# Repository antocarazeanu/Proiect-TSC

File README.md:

## README - Proiect TSC 2025
## Titlu Proiect: Ebook Reader
## Nume: Carazeanu Antonio-Christian
## Grupa: 332CC

Cuprins:

0. Descrierea generala
1. Diagrama bloc
2. BOM - Bill of Materials
3. Arhitectura hardware
4. Pini utilizați pe ESP32-C6 și justificare
5. Probleme intampinate
6. Observatii

## 0. Descriere Generală:
Proiectul a avut ca scop realizarea unui Ebook Reader ieftin si OpenSource din
perspectiva unui Arhitect de Sistem. Acest dispozitiv poate fi scos pentru a fi
produs in masa.

Am urmat toți pașii standard de proiectare, începând de la schematic, continuând
cu layout-ul PCB, modelare 3D și integrarea finală într-o carcasă.

## 1. Diagrama bloc

## 2. BOM - Bill of Materials
| Device | Value | Check_Price | Datasheet |
|--------|-------|-------------|-----------|
| ADAFRUIT_LEDCHIP-LED0603 | - | [Link](https://www.snapeda.com/parts/KP-1608SURCK/Kingbright/view-part/?ref=search&t=LED%200603) | [Link](https://www.snapeda.com/parts/KP-1608SURCK/Kingbright/datasheet/) |
| SJ | - | [Link](https://grabcad.com/library/solder-jumpers-1) | - |
| EAGLE-LTSPICE_C | 0.1uF/50V | [Link](https://componentsearchengine.com/part-view/CC0402MRX5R5BB106/YAGEO) | [Link](https://componentsearchengine.com/Datasheets/2/CC0402MRX5R5BB106.pdf) |
| ESP32_WROVER_EAGLE-LTSPICE_R | 0.47 | [Link](https://componentsearchengine.com/part-view/R0402%201%25%20100%20K%20(RC0402FR-07100KL)/YAGEO) | [Link](https://www.yageo.com/upload/media/product/products/datasheet/rchip/PYu-RC_Group_51_RoHS_L_12.pdf) |
| ESP32_WROVER_EAGLE-LTSPICE_R | 100K | [Link](https://componentsearchengine.com/part-view/R0402%201%25%20100%20K%20(RC0402FR-07100KL)/YAGEO) | [Link](https://www.yageo.com/upload/media/product/products/datasheet/rchip/PYu-RC_Group_51_RoHS_L_12.pdf) |
| EAGLE-LTSPICE_C | 100nF | [Link](https://componentsearchengine.com/part-view/CC0402MRX5R5BB106/YAGEO) | [Link](https://componentsearchengine.com/Datasheets/2/CC0402MRX5R5BB106.pdf) |
| RCL_CPOL-EUCT3528 | 100uF TANT | [Link](https://www.snapeda.com/parts/TAJB475K025RNJ/AVX/view-part/?ref=dk&t=capacitor%203528&con_ref=None) | [Link](https://s3.amazonaws.com/snapeda/datasheet/TAJB475K025RNJ_AVX.pdf) |
| ESP32_WROVER_EAGLE-LTSPICE_R | 10K | [Link](https://componentsearchengine.com/part-view/R0402%201%25%20100%20K%20(RC0402FR-07100KL)/YAGEO) | [Link](https://www.yageo.com/upload/media/product/products/datasheet/rchip/PYu-RC_Group_51_RoHS_L_12.pdf) |
| EAGLE-LTSPICE_C | 10uF | [Link](https://componentsearchengine.com/part-view/CC0402MRX5R5BB106/YAGEO) | [Link](https://componentsearchengine.com/Datasheets/2/CC0402MRX5R5BB106.pdf) |
| 112A-TAAR-R03_ATTEND | 112A-TAAR-R03_ATTEND | [Link](https://store.comet.srl.ro/Catalogue/Product/43497/) | [Link](https://store.comet.bg/download-file.php?id=8824) |
| ESP32_WROVER_EAGLE-LTSPICE_R | 15 | [Link](https://componentsearchengine.com/part-view/R0402%201%25%20100%20K%20(RC0402FR-07100KL)/YAGEO) | [Link](https://www.yageo.com/upload/media/product/products/datasheet/rchip/PYu-RC_Group_51_RoHS_L_12.pdf) |
| EAGLE-LTSPICE_C | 1uF | [Link](https://componentsearchengine.com/part-view/CC0402MRX5R5BB106/YAGEO) | [Link](https://componentsearchengine.com/Datasheets/2/CC0402MRX5R5BB106.pdf) |
| EAGLE-LTSPICE_C | 1uF/50V | [Link](https://componentsearchengine.com/part-view/CC0402MRX5R5BB106/YAGEO) | [Link](https://componentsearchengine.com/Datasheets/2/CC0402MRX5R5BB106.pdf) |
| ESP32_WROVER_EAGLE-LTSPICE_R | 2.2 | [Link](https://componentsearchengine.com/part-view/R0402%201%25%20100%20K%20(RC0402FR-07100KL)/YAGEO) | [Link](https://www.yageo.com/upload/media/product/products/datasheet/rchip/PYu-RC_Group_51_RoHS_L_12.pdf) |
| ESP32_WROVER_EAGLE-LTSPICE_R | 200 | [Link](https://componentsearchengine.com/part-view/R0402%201%25%20100%20K%20(RC0402FR-07100KL)/YAGEO) | [Link](https://www.yageo.com/upload/media/product/products/datasheet/rchip/PYu-RC_Group_51_RoHS_L_12.pdf) |
| ESP32_WROVER_SPARKFUN-DISCRETESEMI_MOSFET_PCH-DMG2305UX-7 | 20V/4.2A/52m?/1.4W | [Link](https://componentsearchengine.com/part-view/DMG2305UX-7/Diodes%20Incorporated) | [Link](https://www.diodes.com//assets/Datasheets/DMG2305UX.pdf) |
| ESP32_WROVER_EAGLE-LTSPICE_R | 2K | [Link](https://componentsearchengine.com/part-view/R0402%201%25%20100%20K%20(RC0402FR-07100KL)/YAGEO) | [Link](https://www.yageo.com/upload/media/product/products/datasheet/rchip/PYu-RC_Group_51_RoHS_L_12.pdf) |
| EAGLE-LTSPICE_C | 4.7uF | [Link](https://componentsearchengine.com/part-view/CC0402MRX5R5BB106/YAGEO) | [Link](https://componentsearchengine.com/Datasheets/2/CC0402MRX5R5BB106.pdf) |
| EAGLE-LTSPICE_C | 4.7uF/25V | [Link](https://componentsearchengine.com/part-view/CC0402MRX5R5BB106/YAGEO) | [Link](https://componentsearchengine.com/Datasheets/2/CC0402MRX5R5BB106.pdf) |
| ESP32_WROVER_EAGLE-LTSPICE_R | 5k1 | [Link](https://componentsearchengine.com/part-view/R0402%201%25%20100%20K%20(RC0402FR-07100KL)/YAGEO) | [Link](https://www.yageo.com/upload/media/product/products/datasheet/rchip/PYu-RC_Group_51_RoHS_L_12.pdf) |
| 744043680IND_4828-WE-TPC_WRE | 68uH | [Link](https://ro.mouser.com/ProductDetail/Wurth-Elektronik/744043680?qs=PGXP4M47uW6VkZq%252BkzjrHA%3D%3D&_gl=1*5xajdn*_ga*MzY2ODgyMjE4LjE3NDM2NzQxODk.*_ga_15W4STQT4T*MTc0Mzg3MzkxMy40LjAuMTc0Mzg3MzkxNi41Ny4wLjA.) | [Link](https://www.we-online.com/components/products/datasheet/744043680.pdf) |
| BD5229G-TR | BD5229G-TR | [Link](https://componentsearchengine.com/part-view/BD5229G-TR/ROHM%20Semiconductor) | [Link](https://datasheet.datasheetarchive.com/originals/distributors/Datasheets_SAMA/f2b9741ef86007909f138d561a359946.pdf) |
| ESP32_WROVER_BME680_BME680 | BME688 | [Link](https://www.snapeda.com/parts/BME680/Bosch/view-part/?welcome=home) | [Link](https://www.snapeda.com/parts/BME680/Bosch%20Sensortec/datasheet/) |
| BUTTON_CUSYOMV1V2 | BUTTON_CUSYOMV1V2 | [Link](https://industry.panasonic.com/global/en/products/control/switch/light-touch/number/evqpuj02k) | [Link](https://industry.panasonic.com/global/en/downloads?tab=catalog&small_g_cd=203&part_no=EVQPUJ02K) |
| CPH3225A | CPH3225A | [Link](https://www.snapeda.com/parts/CPH3225A/Seiko+Instruments/view-part/?ref=eda) | [Link](https://www.snapeda.com/parts/CPH3225A/Seiko+Instruments/view-part/?ref=eda ) |
| DS3231SN# | DS3231SN# | [Link](https://www.snapeda.com/parts/DS3231SN%23/Analog+Devices/view-part/?ref=eda) | [Link](https://www.snapeda.com/parts/DS3231SN%23/Analog+Devices/view-part/?ref=eda) |
| ESP32-C6-WROOM-1-N8 | ESP32-C6-WROOM-1-N8 | [Link](https://www.snapeda.com/parts/ESP32-C6-WROOM-1-N8/Espressif+Systems/view-part/?ref=eda) | [Link](https://www.snapeda.com/parts/ESP32-C6-WROOM-1-N8/Espressif+Systems/view-part/?ref=eda) |
| ESP32C6_VARISTORCN1812 | ESP32C6_VARISTORCN1812 | [Link](https://www.mouser.co.uk/ProductDetail/EPCOS-TDK/B72520T0350K062?qs=dEfas%2FXlABIszF52uu7vrg%3D%3D) | [Link](https://www.tdk-electronics.tdk.com/inf/75/db/CTVS_14/Surge_protection_series.pdf) |
| ESP32_WROVER_SPARKFUN-IC-POWER_MCP73831 | ESP32_WROVER_SPARKFUN-IC-POWER_MCP73831 | [Link](https://ro.mouser.com/ProductDetail/Microchip-Technology/MCP73831T-2ACI-OT?qs=yUQqVecv4qvbBQBGbHx0Mw%3D%3D) | [Link](https://ro.mouser.com/datasheet/2/268/MCP73831_Family_Data_Sheet_DS20001984H-3441711.pdf) |
| FH34SRJ-24S-0.5SH_99_ | FH34SRJ-24S-0.5SH_99_ | [Link](https://componentsearchengine.com/part-view/FH34SRJ-24S-0.5SH(99)/Hirose) | [Link](https://www.hirose.com/en/product/document?clcode=CL0580-1255-6-99&productname=FH34SRJ-24S-0.5SH(99)&series=FH34SRJ&documenttype=2DDrawing&lang=en&documentid=0000990903) |
| MAX17048G+T10 | MAX17048G+T10 | [Link](https://www.snapeda.com/parts/MAX17048G+T10/Analog+Devices/view-part/?ref=eda) | [Link](https://www.snapeda.com/parts/MAX17048G+T10/Analog+Devices/view-part/?ref=eda) |
| MBR0530. | MBR0530. | [Link](https://www.snapeda.com/parts/MBR0530/Onsemi/view-part/?ref=eda) | [Link](https://www.snapeda.com/parts/MBR0530/ON%20Semiconductor/datasheet/) |
| PGB1010603MR. | PGB1010603MR. | [Link](https://www.snapeda.com/parts/PGB1010603MR/Littelfuse/view-part/?ref=eda) | [Link](https://www.snapeda.com/parts/PGB1010603MR/Littelfuse%20Inc./datasheet/) |
| QWIIC_CONNECTORJS-1MM | QWIIC_RIGHT_ANGLE | [Link](https://www.digikey.lt/en/models/926710 ) | [Link](https://www.digikey.lt/en/models/926710) |
| SAMACSYS_PARTS_USB4110-GF-A | SAMACSYS_PARTS_USB4110-GF-A | [Link](https://componentsearchengine.com/part-view/USB4110-GF-A/GCT%20(GLOBAL%20CONNECTOR%20TECHNOLOGY)) | [Link](https://gct.co/files/drawings/usb4110.pdf) |
| ESP32_WROVER_AVX---SD0805S020S1R0_AVX_SD0805S020S1R0_0_0AVX_SD0805S020S1R0_0_0 | SD0805S020S1R0 | [Link](https://ro.mouser.com/ProductDetail/KYOCERA-AVX/SD0805S020S1R0?qs=jCA%252BPfw4LHbpkAoSnwrdjw%3D%3D) | [Link](http://datasheets.avx.com/schottky.pdf) |
| SI1308EDL-T1-GE3 | SI1308EDL-T1-GE3 | [Link](https://www.snapeda.com/parts/SI1308EDL-T1-GE3/Vishay+Siliconix/view-part/?ref=eda) | [Link](https://www.snapeda.com/parts/SI1308EDL-T1-GE3/Vishay+Siliconix/view-part/?ref=eda) |
| TPV1 | TPV1 | Custom made | - |
| USBLC6-2SC6Y | USBLC6-2SC6Y | [Link](https://www.snapeda.com/parts/USBLC6-2SC6Y/STMicroelectronics/view-part/?ref=eda) | [Link](https://www.snapeda.com/parts/USBLC6-2SC6Y/STMicroelectronics/view-part/?ref=eda) |
| W25Q512JVEIQ | W25Q512JVEIQ | [Link](https://www.snapeda.com/parts/W25Q512JVEIQ/Winbond+Electronics/view-part/?ref=eda) | [Link](https://www.snapeda.com/parts/W25Q512JVEIQ/Winbond+Electronics/view-part/?ref=eda) |
| XC6220A331MR-G | XC6220A331MR-G | [Link](https://componentsearchengine.com/part-view/XC6220A331MR-G/Torex) | [Link](https://product.torexsemi.com/system/files/series/xc6220.pdf) |

## 3. Arhitectura Hardware

Descriem în continuare componentele hardware cheie și funcționalitatea acestora în cadrul dispozitivului:

| Nr. | Componentă Principală                   |
|-----|------------------------------------------|
| 1   | Microcontroller – ESP32-C6-WROOM-1       |
| 2   | Ecran E-Ink – Waveshare WSH-13187, 7.5”  |
| 3   | Senzor Ambiental – Bosch BME688          |
| 4   | Sistem de Alimentare și Baterie          |
| 5   | Butoane de Control – 3x Tactile Switch   |
| 6   | Conector USB-C                           |
| 7   | Port Extensie Qwiic / STEMMA QT (I²C)    |
| 8   | Soclu MicroSD – Attend 112A-TAAR-R03     |
| 9   | Ceas Timp Real (RTC) – DS3231            |

### 3.1. Unitatea Centrală – Microcontroller ESP32-C6-WROOM-1

-   **Unitate de Procesare:** RISC-V pe 32 de biți, tactat la 160MHz
-   **Memorie:** 512KB SRAM integrat + 8MB memorie flash externă (model W25Q512JVEIQ)
-   **Opțiuni de Comunicare:** Wi-Fi 6 (standard 802.11ax), Bluetooth 5 LE, interfață USB 2.0 Full-Speed
-   **Interfețe Disponibile:** SPI, I²C, UART, multiple porturi GPIO
-   **Consum Energetic:** Sub 50µA în modul deep sleep; diverse moduri de consum redus sunt implementate
-   **Funcții de Securitate:** Include secure boot, criptare pentru memoria flash și accelerare hardware pentru criptografie

### 3.2. Afișajul Electronic – Ecran E-Ink Waveshare WSH-13187, 7.5”

-   **Rezoluție:** 800x480 pixeli, imagine monocromă
-   **Modalitate de Conectare:** Interfață SPI (4 fire) plus linii de control CS, DC, RST, BUSY
-   **Consum Energetic:** Aproximativ 15–25mA în timpul actualizării imaginii; consum neglijabil în stare statică
-   **Rațiunea Alegerii:** Consumul energetic aproape nul când imaginea nu se schimbă, optim pentru aplicații tip e-reader

### 3.3. Senzorul Ambiental Integrat – Bosch BME688

-   **Parametri Măsurați:** Temperatură, Umiditate relativă, Presiune atmosferică, Indice al Calității Aerului (estimare eCO2, TVOC)
-   **Acuratețe:** ±1°C pentru temperatură, ±3% pentru umiditate, ±1 hPa pentru presiune
-   **Modalitate de Conectare:** Interfață I²C (operând la 400kHz)
-   **Consum Energetic:** 2.1µA în standby, maxim 3.6mA în timpul măsurătorilor active
-   **Rațiunea Alegerii:** Soluție compactă multi-senzor, potrivită pentru monitorizarea condițiilor ambientale

### 3.4. Sistemul de Alimentare și Gestionarea Energiei

-   **Sursa de Energie:** Acumulator Li-Po de 3.7V cu o capacitate de 2500mAh
-   **Monitorizare Baterie:** Circuit integrat MAX17048 (comunică prin I²C)
-   **Circuit de Încărcare:** MCP73831 – permite încărcarea cu 5V/1A via portul USB-C
-   **Regulator de Tensiune:** LDO ce furnizează o tensiune stabilă de 3.3V pentru întregul circuit
-   **Consum Total Estimativ:**
    -   În mod activ: între 100 și 150mA
    -   În mod deep sleep: sub 50µA

### 3.5. Interfața cu Utilizatorul – 3x Butoane Tactile

-   **Model Buton:** Panasonic EVQ-Q2A03W
-   **Conectare Electrică:** Legate la pini GPIO, cu circuit de debounce hardware (filtru RC)
-   **Funcționalități Asignate:** Navigare prin meniuri, avansare/revenire pagină, confirmare acțiuni

### 3.6. Conectorul USB-C

-   **Funcționalități Principale:** Încărcarea bateriei și transferul de date (conform standardului USB 2.0)
-   **Măsuri de Protecție:** Protecție ESD integrată și terminații conforme standardului
-   **Posibilități Suplimentare:** Actualizări software OTA (Over-The-Air) via Wi-Fi sau actualizare firmware prin conexiune USB

### 3.7. Portul de Extensie Qwiic / STEMMA QT (I²C)

-   **Configurație Pini:** VCC (Alimentare), GND (Masă), SDA (Date I²C), SCL (Ceas I²C)
-   **Scop/Beneficii:** Permite conectarea rapidă a modulelor și senzorilor externi compatibili I²C

### 3.8. Soclul pentru Card MicroSD – Attend 112A-TAAR-R03

-   **Rol Principal:** Oferă spațiu de stocare extern (pentru cărți electronice, fișiere jurnal, firmware etc.)
-   **Modalitate de Conectare:** Interfață SPI

### 3.9. Ceasul Timp Real (RTC) – DS3231

-   **Acuratețe:** Deviație maximă de ±2 părți per milion (ppm)
-   **Modalitate de Conectare:** Interfață I²C
-   **Alimentare de Backup:** Asigurată de un supercapacitor

---

### Protocoale de Comunicare și Interfețe Utilizate

| Protocol/Interfață | Componente Conectate                                |
|--------------------|-----------------------------------------------------|
| **SPI**            | Ecran E-Paper, Memorie Flash externă, Card SD (SPI) |
| **I²C**            | Senzor BME688, Fuel Gauge MAX17048, RTC DS3231, Port Qwiic/Stemma |
| **USB**            | Încărcare și comunicație de date via USB-C         |
| **GPIO**           | Butoane, Linii control afișaj, Activare încărcare   |

---

### Profil de Consum Energetic (Estimări)

| Stare/Componentă       | Consum Estimativ   |
|------------------------|--------------------|
| ESP32-C6 (mod activ)   | 80–100mA           |
| Actualizare E-Paper    | 15–25mA            |
| Senzor BME688 (activ)  | 3.6mA              |
| Fuel Gauge MAX17048    | ~50µA              |
| RTC DS3231             | 3.5mA / 1µA backup |
| Deep Sleep (Total)     | <50–100µA          |

---

### Specificații Fizice și Constructive

-   **Mărimi Fizice:** 175 x 114 x 10 mm
-   **Masa Dispozitivului:** Aproximativ 250g
-   **Material Carcasă:** ABS sau policarbonat, cu design ergonomic
-   **Montare Afișaj:** Integrat într-un decupaj specific al carcasei
-   **Detalii de Fabricație:** PCB cu 2 straturi, finisaj ENIG, carcasă obținută prin injecție de plastic

## 4. Pini utilizați pe ESP32-C6 și justificare

| Pin ESP32-C6 | Componentă / Semnal                | De ce?                                                                 |
|--------------|-------------------------------------|------------------------------------------------------------------------|
| GPIO1        | I²C SDA (BME688, MAX17048, DS3231, Qwiic) | Linie partajată I²C – economisește pini și permite extinderea facilă |
| GPIO2        | I²C SCL (BME688, MAX17048, DS3231, Qwiic) | Clock I²C pentru toți senzorii și extensii Qwiic                     |
| GPIO5        | SPI MISO (E-Paper, Flash extern)    | Linie comună de intrare date în SPI                                   |
| GPIO6        | SPI MOSI (E-Paper, Flash extern)    | Linie de ieșire date către e-paper și flash                           |
| GPIO7        | SPI CLK                             | Semnal de clock pentru magistrala SPI                                 |
| GPIO8        | E-Paper CS                          | Selectează afișajul pe magistrala SPI                                 |
| GPIO9        | E-Paper DC (Data/Command)           | Comută între comandă și date către e-paper                            |
| GPIO10       | E-Paper RST                         | Reset hardware e-paper                                                |
| GPIO11       | E-Paper BUSY                        | Pin de stare (ocupat/liber) de la display                             |
| GPIO12       | Button #1                           | Intrare digitală pentru navigare pagină înainte                      |
| GPIO13       | Button #2                           | Intrare digitală pentru navigare pagină înapoi                       |
| GPIO14       | Button #3                           | Intrare digitală pentru selectare/opțiune                            |
| GPIO15       | MAX17048 ALERT (opțional)           | Pin de alertă nivel scăzut baterie                                    |
| GPIO16       | USB D+ (intern la USB PHY)          | Linie USB 2.0 (fixă pe ESP32-C6)                                      |
| GPIO17       | USB D- (intern la USB PHY)          | Linie USB 2.0 (fixă pe ESP32-C6)                                      |
| GPIO18       | LED Status (opțional)               | Indicator pentru activitate Wi-Fi, charging, notificări               |
| GPIO19       | SD Card CS                          | Selectare chip pentru card microSD (SPI)                              |
| GPIO20       | SD Card MISO                        | Citire date de pe card microSD                                        |
| GPIO21       | SD Card MOSI                        | Scriere date pe card microSD                                          |
| GPIO4        | SD Card CLK                         | Semnal de clock pentru card microSD (SPI)                             |

## 5. Probleme intampinate
1) La partea de 3D am întâmpinat o problemă semnificativă — modelele 3D ale rezistențelor și condensatoarelor nu se actualizau automat în PCB atunci când încercam să folosesc funcția Replace Package. Pentru a rezolva această problemă, a trebuit să adaug manual modelele 3D custom realizate pentru fiecare componentă în parte.

2) Bobina si mufa USB au avut dimensiunea pad-urilor mai mica decat grosimea firelor, marint astfel pad-urile din footprint pentru a putea face lipirea.

## 6. Observatii
Un proiect mult prea muncitoresc care nu merita doar 2pct din nota.
Timp de lucru aprox ~70h

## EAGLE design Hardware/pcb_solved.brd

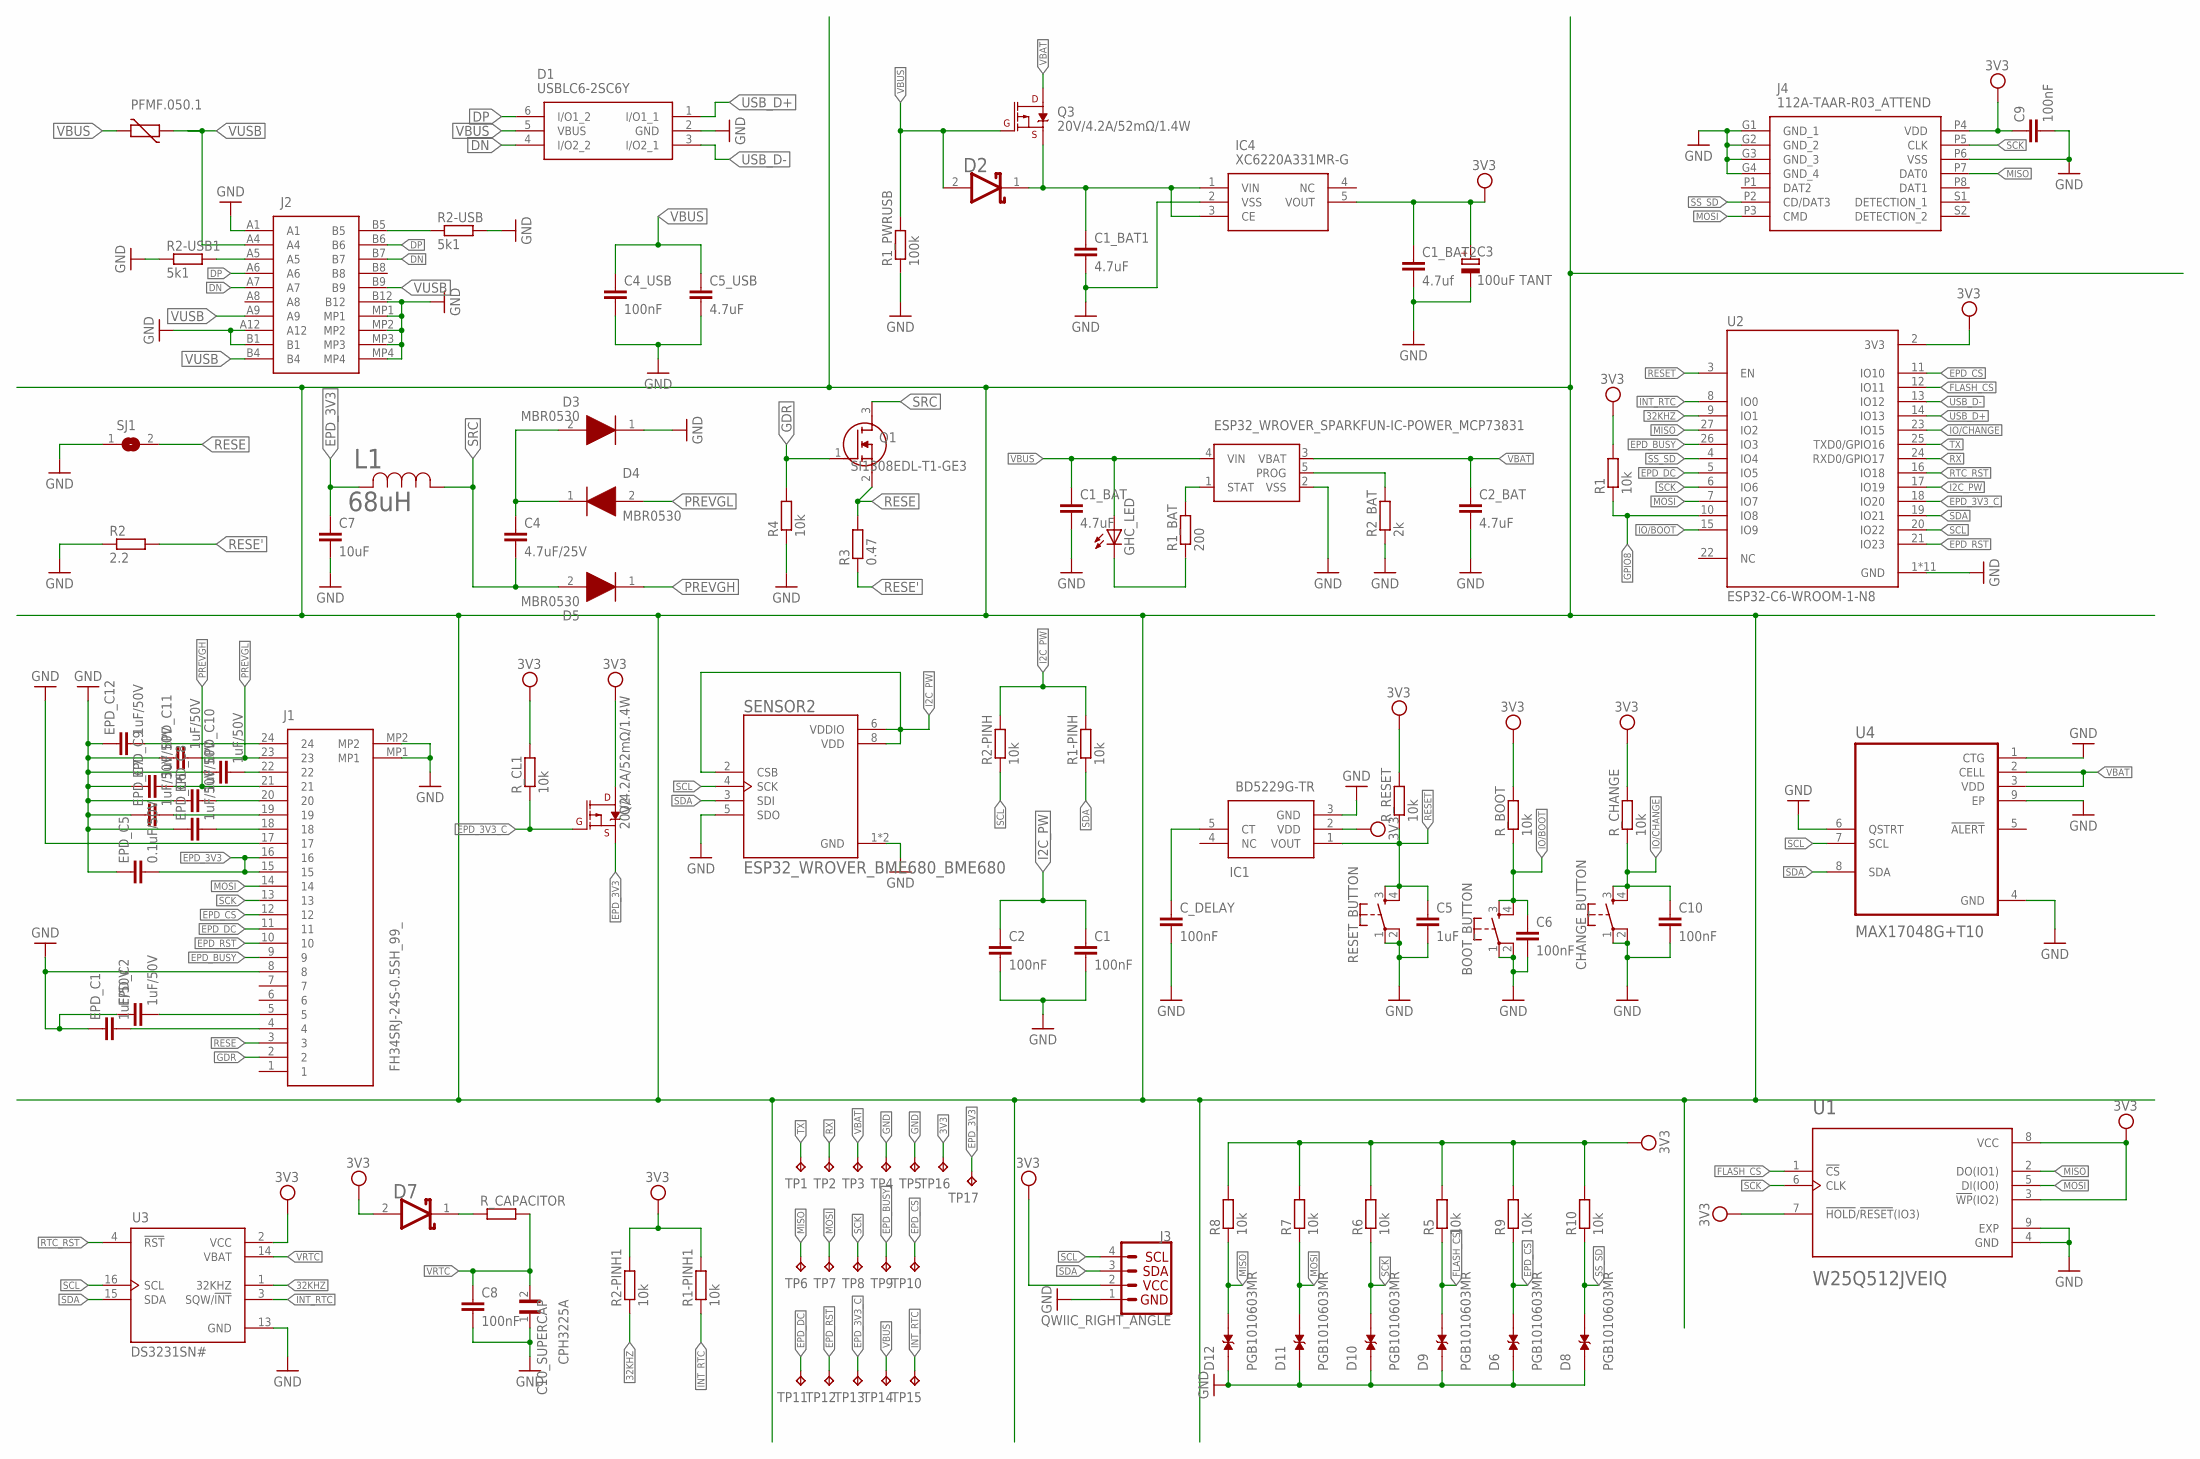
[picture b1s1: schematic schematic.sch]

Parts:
BOOT_BUTTON: BUTTON_CUSYOMV1; MYBUTTON
C1, C2, C4_USB, C6, C8, C9, C10: 100nF; ESP32_WROVER_EAGLE-LTSPICE_C0402
C1_BAT, C1_BAT1, C2_BAT: 4.7uF; EAGLE-LTSPICE_C0402
C1_BAT2: 4.7uf; EAGLE-LTSPICE_C0402
C3: 100uF TANT; RCL_CT3528
C4: 4.7uF/25V; ESP32_WROVER_EAGLE-LTSPICE_C0402
C5: 1uF; ESP32_WROVER_EAGLE-LTSPICE_C0402
C5_USB: 4.7uF; ESP32_WROVER_EAGLE-LTSPICE_C0402
C7: 10uF; ESP32_WROVER_EAGLE-LTSPICE_C0402
C10_SUPERCAP: CPH3225A; CAPCP3225X100N
CHANGE_BUTTON: BUTTON_CUSYOMV1; MYBUTTON
C_DELAY: 100nF; ESP32_WROVER_EAGLE-LTSPICE_C0402
D1: USBLC6-2SC6Y; SOT95P280X145-6N
D2, D7: ESP32_WROVER_AVX---SD0805S020S1R0_AVX_SD0805S020S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; ESP32_WROVER_AVX---SD0805S020S1R0_AVX_SD0805S020S1R0_0
D3, D4, D5: MBR0530; SOD3716X135N
D6, D8, D9, D10, D11, D12: PGB1010603MR; DIOC1608X36N
EPD_C1, EPD_C2, EPD_C6, EPD_C7, EPD_C8, EPD_C9, EPD_C10, EPD_C11, EPD_C12: 1uF/50V; ESP32_WROVER_EAGLE-LTSPICE_C0402
EPD_C5: 0.1uF/50V; ESP32_WROVER_EAGLE-LTSPICE_C0402
GHC_LED: ADAFRUIT_LEDCHIP-LED0603; ADAFRUIT_CHIP-LED0603
IC1: BD5229G-TR; SOT95P280X125-5N
IC4: XC6220A331MR-G; SOT95P280X120-5N
J1: FH34SRJ-24S-0.5SH_99_; FH34SRJ24S05SH99
J2: SAMACSYS_PARTS_USB4110-GF-A; SAMACSYS_PARTS_USB4110GFA
J3: QWIIC_RIGHT_ANGLE; JST04_1MM_RA
J4: 112A-TAAR-R03_ATTEND; 112ATAARR03ATTEND
L1: 68uH; IND_4828-WE-TPC_WRE
PFMF.050.1: ESP32C6_VARISTORCN1812; ESP32C6_VARISTOR_CT/CN1812
Q1: SI1308EDL-T1-GE3; SOT65P210X110-3N
Q2, Q3: 20V/4.2A/52mΩ/1.4W; ESP32_WROVER_SPARKFUN-DISCRETESEMI_SOT23-3
R1, R1-PINH, R1-PINH1, R2-PINH, R2-PINH1, R4, R5, R6, R7, R8, R9, R10: 10k; ESP32_WROVER_EAGLE-LTSPICE_R0402
R1_BAT: 200; ESP32_WROVER_EAGLE-LTSPICE_R0402
R1_PWRUSB: 100k; ESP32_WROVER_EAGLE-LTSPICE_R0402
R2: 2.2; ESP32_WROVER_EAGLE-LTSPICE_R0402
R2-USB, R2-USB1: 5k1; ESP32_WROVER_EAGLE-LTSPICE_R0402
R2_BAT: 2k; ESP32_WROVER_EAGLE-LTSPICE_R0402
R3: 0.47; ESP32_WROVER_EAGLE-LTSPICE_R0402
RESET_BUTTON: BUTTON_CUSYOMV1; MYBUTTON
R_BOOT: 10k; ESP32_WROVER_EAGLE-LTSPICE_R0402
R_CAPACITOR: ESP32_WROVER_EAGLE-LTSPICE_RR0402; ESP32_WROVER_EAGLE-LTSPICE_R0402
R_CHANGE: 10k; ESP32_WROVER_EAGLE-LTSPICE_R0402
R_CL1: 10k; ESP32_WROVER_EAGLE-LTSPICE_R0402
R_RESET: 10k; ESP32_WROVER_EAGLE-LTSPICE_R0402
SENSOR2: ESP32_WROVER_BME680_BME680; ESP32_WROVER_BME680_PSON80P300X300X100-8N
SJ1: SJ
TP1, TP2, TP3, TP4, TP5, TP6, TP7, TP8, TP9, TP10, TP11, TP12, TP13, TP14, TP15, TP16, TP17: TPTP20R; TP20R
U: ESP32_WROVER_SPARKFUN-IC-POWER_MCP73831; ESP32_WROVER_SPARKFUN-IC-POWER_SOT23-5
U1: W25Q512JVEIQ; SON127P600X800X80-9N
U2: ESP32-C6-WROOM-1-N8; XCVR_ESP32-C6-WROOM-1-N8
U3: DS3231SN#; SOIC127P1032X265-16N
U4: MAX17048G+T10; SON50P200X200X80-9N

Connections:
3V3: C1_BAT2.1, C3.+, C9.1, D7.2 (ANODE), IC1.2 (VDD), IC4.5 (VOUT), J3.2, J4.P4 (VDD), Q2.3 (D), R1.2, R1-PINH1.2, R2-PINH1.2, R5.2, R6.2, R7.2, R8.2, R9.2, R10.2, R_BOOT.2, R_CHANGE.2, R_CL1.2, R_RESET.2, TP16.TP, U1.3 (!WP!(IO2)), U1.7 (!HOLD!/!RESET!(IO3)), U1.8 (VCC), U2.2 (3V3), U3.2 (VCC)
32KHZ: R2-PINH1.1, U2.9 (IO1), U3.1 (32KHZ)
DN: D1.4 (I/O2_2), J2.A7, J2.B7
DP: D1.6 (I/O1_2), J2.A6, J2.B6
EPD_3V3: C7.1, EPD_C5.2, J1.15, J1.16, L1.2, Q2.2 (S), TP17.TP
EPD_3V3_C: Q2.1 (G), R_CL1.1, TP13.TP, U2.18 (IO20)
EPD_BUSY: J1.9, TP9.TP, U2.26 (IO3)
EPD_CS: D6.2, J1.12, R9.1, TP10.TP, U2.11 (IO10)
EPD_DC: J1.11, TP11.TP, U2.5 (IO5)
EPD_RST: J1.10, TP12.TP, U2.21 (IO23)
FLASH_CS: D9.2, R5.1, U1.1 (!CS), U2.12 (IO11)
GDR: J1.2, Q1.1 (G), R4.2
GND: BOOT_BUTTON.1, BOOT_BUTTON.2, C1.2, C1_BAT.2, C1_BAT1.2, C1_BAT2.2, C2.2, C2_BAT.2, C3.-, C4_USB.2, C5.2, C5_USB.2, C6.2, C7.2, C8.2, C9.2, C10.2, C10_SUPERCAP.1, CHANGE_BUTTON.1, CHANGE_BUTTON.2, C_DELAY.2, D1.2 (GND), D3.1 (K), D6.1, D8.1, D9.1, D10.1, D11.1, D12.1, EPD_C1.1, EPD_C2.1, EPD_C5.1, EPD_C6.1, EPD_C7.1, EPD_C8.1, EPD_C9.1, EPD_C10.1, EPD_C11.1, EPD_C12.1, IC1.3 (GND), IC4.2 (VSS), J1.8, J1.17, J1.MP1, J1.MP2, J2.A1, J2.A12, J2.B1, J2.B12, J2.MP1, J2.MP2, J2.MP3, J2.MP4, J3.1, J4.G1 (GND_1), J4.G2 (GND_2), J4.G3 (GND_3), J4.G4 (GND_4), J4.P6 (VSS), R1_PWRUSB.1, R2.1, R2-USB.2, R2-USB1.1, R2_BAT.1, R4.1, RESET_BUTTON.1, RESET_BUTTON.2, SENSOR2.1 (GND), SENSOR2.5 (SDO), SENSOR2.7 (GND), SJ1.1, TP4.TP, TP5.TP, U.2 (VSS), U1.4 (GND), U1.9 (EXP), U2.1 (GND), U2.28 (GND), U2.29_1 (GND), U2.29_2 (GND), U2.29_3 (GND), U2.29_4 (GND), U2.29_5 (GND), U2.29_6 (GND), U2.29_7 (GND), U2.29_8 (GND), U2.29_9 (GND), U3.13 (GND), U4.1 (CTG), U4.4 (GND), U4.6 (QSTRT), U4.9 (EP)
GPIO8: R1.1, U2.10 (IO8)
I2C_PW: C1.1, C2.1, R1-PINH.2, R2-PINH.2, SENSOR2.2 (CSB), SENSOR2.6 (VDDIO), SENSOR2.8 (VDD), U2.17 (IO19)
INT_RTC: R1-PINH1.1, TP15.TP, U2.8 (IO0), U3.3 (SQW/!INT)
IO/BOOT: BOOT_BUTTON.3, BOOT_BUTTON.4, C6.1, R_BOOT.1, U2.15 (IO9)
IO/CHANGE: C10.1, CHANGE_BUTTON.3, CHANGE_BUTTON.4, R_CHANGE.1, U2.23 (IO15)
MISO: D12.2, J4.P7 (DAT0), R8.1, TP6.TP, U1.2 (DO(IO1)), U2.27 (IO2)
MOSI: D11.2, J1.14, J4.P3 (CMD), R7.1, TP7.TP, U1.5 (DI(IO0)), U2.7 (IO7)
unnamed: J2.A5, R2-USB1.2
unnamed: J2.B5, R2-USB.1
unnamed: C4.1, D3.2 (A), D4.1 (K)
unnamed: EPD_C2.2, J1.5
unnamed: EPD_C1.2, J1.4
unnamed: EPD_C6.2, J1.18
unnamed: EPD_C8.2, J1.20
unnamed: EPD_C7.2, J1.19
unnamed: EPD_C12.2, J1.24
unnamed: EPD_C10.2, J1.22
unnamed: D7.1 (CATHODE), R_CAPACITOR.1
unnamed: C1_BAT1.1, D2.1 (CATHODE), IC4.1 (VIN), IC4.3 (CE), Q3.2 (S)
unnamed: R1_BAT.2, U.1 (STAT)
unnamed: GHC_LED.C, R1_BAT.1
unnamed: C_DELAY.1, IC1.5 (CT)
unnamed: R2_BAT.2, U.5 (PROG)
PREVGH: D5.1 (K), EPD_C9.2, J1.21
PREVGL: D4.2 (A), EPD_C11.2, J1.23
RESE: J1.3, Q1.2 (S), R3.2, SJ1.2
RESE': R2.2, R3.1
RESET: C5.1, IC1.1 (VOUT), RESET_BUTTON.3, RESET_BUTTON.4, R_RESET.1, U2.3 (EN)
RTC_RST: U2.16 (IO18), U3.4 (!RST)
RX: TP2.TP, U2.24 (RXD0/GPIO17)
SCK: D10.2, J1.13, J4.P5 (CLK), R6.1, TP8.TP, U1.6 (CLK), U2.6 (IO6)
SCL: J3.4, R2-PINH.1, SENSOR2.4 (SCK), U2.20 (IO22), U3.16 (SCL), U4.7 (SCL)
SDA: J3.3, R1-PINH.1, SENSOR2.3 (SDI), U2.19 (IO21), U3.15 (SDA), U4.8 (SDA)
SRC: C4.2, D5.2 (A), L1.1, Q1.3 (D)
SS_SD: D8.2, J4.P2 (CD/DAT3), R10.1, U2.4 (IO4)
TX: TP1.TP, U2.25 (TXD0/GPIO16)
USB_D+: D1.1 (I/O1_1), U2.14 (IO13)
USB_D-: D1.3 (I/O2_1), U2.13 (IO12)
VBAT: C2_BAT.1, Q3.3 (D), TP3.TP, U.3 (VBAT), U4.2 (CELL), U4.3 (VDD)
VBUS: C1_BAT.1, C4_USB.1, C5_USB.1, D1.5 (VBUS), D2.2 (ANODE), GHC_LED.A, PFMF.050.1.2, Q3.1 (G), R1_PWRUSB.2, TP14.TP, U.4 (VIN)
VRTC: C8.1, C10_SUPERCAP.2, R_CAPACITOR.2, U3.14 (VBAT)
VUSB: J2.A4, J2.A9, J2.B4, J2.B9, PFMF.050.1.1

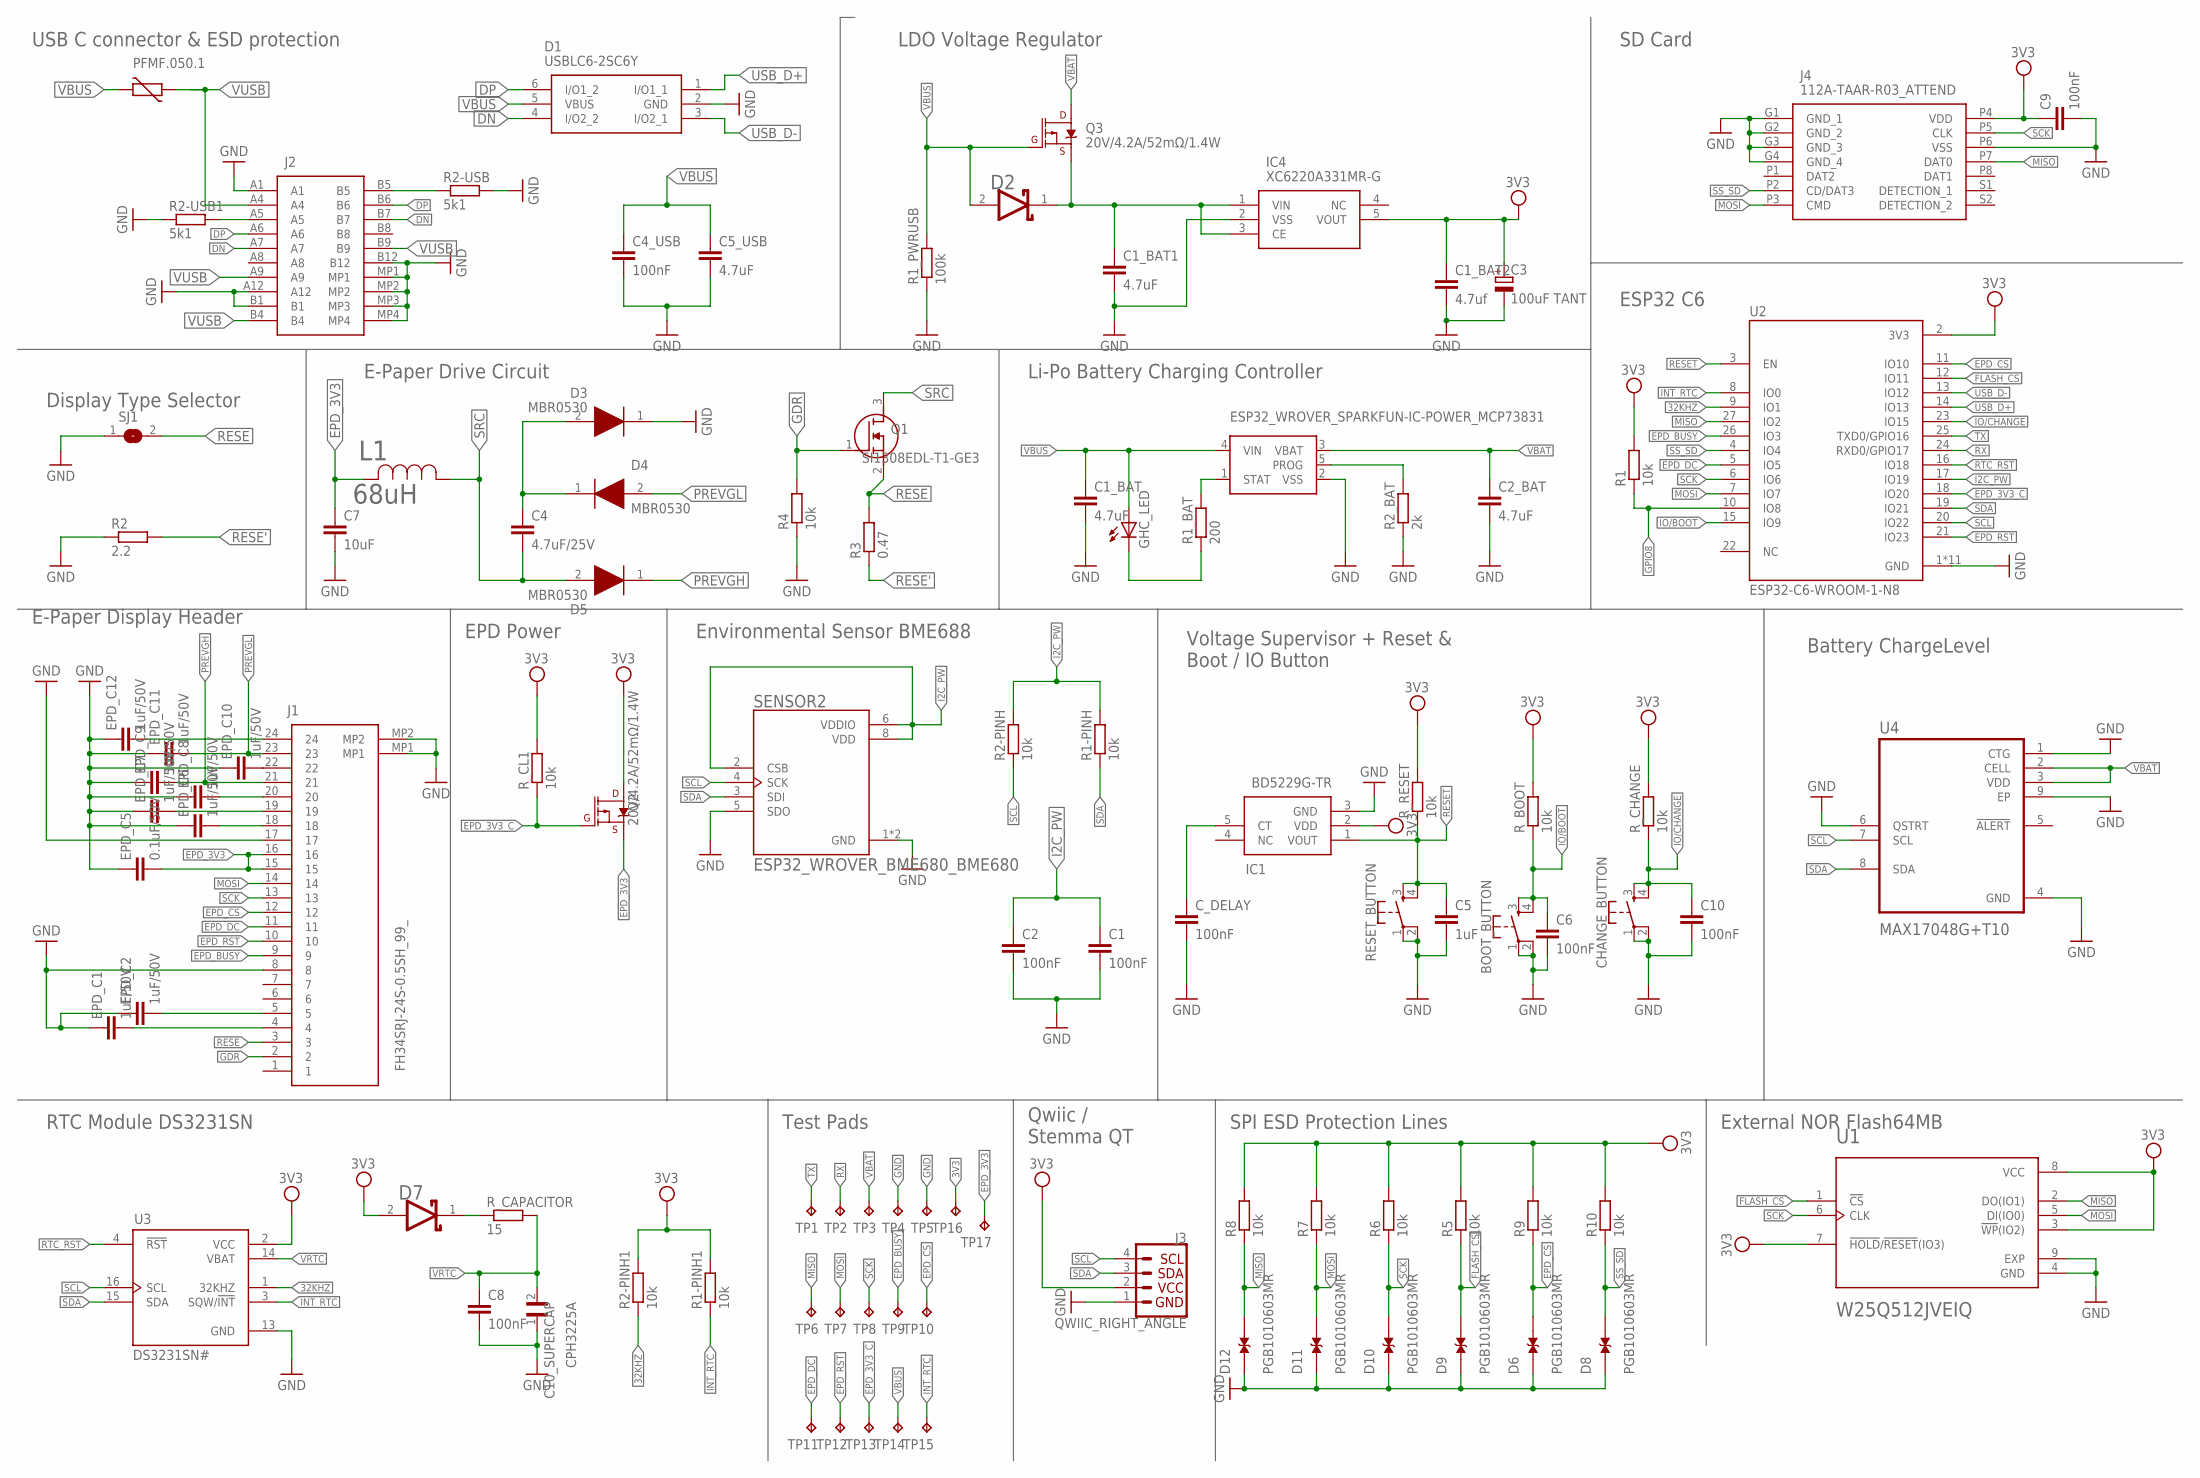
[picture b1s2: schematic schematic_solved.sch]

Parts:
BOOT_BUTTON: BUTTON_CUSYOMV1; MYBUTTON
C1, C2, C4_USB, C6, C8, C9, C10: 100nF; ESP32_WROVER_EAGLE-LTSPICE_C0402
C1_BAT, C1_BAT1, C2_BAT: 4.7uF; EAGLE-LTSPICE_C0402
C1_BAT2: 4.7uf; EAGLE-LTSPICE_C0402
C3: 100uF TANT; RCL_CT3528
C4: 4.7uF/25V; ESP32_WROVER_EAGLE-LTSPICE_C0402
C5: 1uF; ESP32_WROVER_EAGLE-LTSPICE_C0402
C5_USB: 4.7uF; ESP32_WROVER_EAGLE-LTSPICE_C0402
C7: 10uF; ESP32_WROVER_EAGLE-LTSPICE_C0402
C10_SUPERCAP: CPH3225A; CAPCP3225X100N
CHANGE_BUTTON: BUTTON_CUSYOMV1; MYBUTTON
C_DELAY: 100nF; ESP32_WROVER_EAGLE-LTSPICE_C0402
D1: USBLC6-2SC6Y; SOT95P280X145-6N
D2, D7: ESP32_WROVER_AVX---SD0805S020S1R0_AVX_SD0805S020S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; ESP32_WROVER_AVX---SD0805S020S1R0_AVX_SD0805S020S1R0_0
D3, D4, D5: MBR0530; SOD3716X135N
D6, D8, D9, D10, D11, D12: PGB1010603MR; DIOC1608X36N
EPD_C1, EPD_C2, EPD_C6, EPD_C7, EPD_C8, EPD_C9, EPD_C10, EPD_C11, EPD_C12: 1uF/50V; ESP32_WROVER_EAGLE-LTSPICE_C0402
EPD_C5: 0.1uF/50V; ESP32_WROVER_EAGLE-LTSPICE_C0402
GHC_LED: ADAFRUIT_LEDCHIP-LED0603; ADAFRUIT_CHIP-LED0603
IC1: BD5229G-TR; SOT95P280X125-5N
IC4: XC6220A331MR-G; SOT95P280X120-5N
J1: FH34SRJ-24S-0.5SH_99_; FH34SRJ24S05SH99
J2: SAMACSYS_PARTS_USB4110-GF-A; SAMACSYS_PARTS_USB4110GFA
J3: QWIIC_RIGHT_ANGLE; JST04_1MM_RA
J4: 112A-TAAR-R03_ATTEND; 112ATAARR03ATTEND
L1: 68uH; IND_4828-WE-TPC_WRE
PFMF.050.1: ESP32C6_VARISTORCN1812; ESP32C6_VARISTOR_CT/CN1812
Q1: SI1308EDL-T1-GE3; SOT65P210X110-3N
Q2, Q3: 20V/4.2A/52mΩ/1.4W; ESP32_WROVER_SPARKFUN-DISCRETESEMI_SOT23-3
R1, R1-PINH, R1-PINH1, R2-PINH, R2-PINH1, R4, R5, R6, R7, R8, R9, R10: 10k; ESP32_WROVER_EAGLE-LTSPICE_R0402
R1_BAT: 200; ESP32_WROVER_EAGLE-LTSPICE_R0402
R1_PWRUSB: 100k; ESP32_WROVER_EAGLE-LTSPICE_R0402
R2: 2.2; ESP32_WROVER_EAGLE-LTSPICE_R0402
R2-USB, R2-USB1: 5k1; ESP32_WROVER_EAGLE-LTSPICE_R0402
R2_BAT: 2k; ESP32_WROVER_EAGLE-LTSPICE_R0402
R3: 0.47; ESP32_WROVER_EAGLE-LTSPICE_R0402
RESET_BUTTON: BUTTON_CUSYOMV1; MYBUTTON
R_BOOT: 10k; ESP32_WROVER_EAGLE-LTSPICE_R0402
R_CAPACITOR: 15; ESP32_WROVER_EAGLE-LTSPICE_R0402
R_CHANGE: 10k; ESP32_WROVER_EAGLE-LTSPICE_R0402
R_CL1: 10k; ESP32_WROVER_EAGLE-LTSPICE_R0402
R_RESET: 10k; ESP32_WROVER_EAGLE-LTSPICE_R0402
SENSOR2: ESP32_WROVER_BME680_BME680; ESP32_WROVER_BME680_PSON80P300X300X100-8N
SJ1: SJ
TP1, TP2, TP3, TP4, TP5, TP6, TP7, TP8, TP9, TP10, TP11, TP12, TP13, TP14, TP15, TP16, TP17: TPTP20R; TP20R
U: ESP32_WROVER_SPARKFUN-IC-POWER_MCP73831; ESP32_WROVER_SPARKFUN-IC-POWER_SOT23-5
U1: W25Q512JVEIQ; SON127P600X800X80-9N
U2: ESP32-C6-WROOM-1-N8; XCVR_ESP32-C6-WROOM-1-N8
U3: DS3231SN#; SOIC127P1032X265-16N
U4: MAX17048G+T10; SON50P200X200X80-9N

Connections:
3V3: C1_BAT2.1, C3.+, C9.1, D7.2 (ANODE), IC1.2 (VDD), IC4.5 (VOUT), J3.2, J4.P4 (VDD), Q2.3 (D), R1.2, R1-PINH1.2, R2-PINH1.2, R5.2, R6.2, R7.2, R8.2, R9.2, R10.2, R_BOOT.2, R_CHANGE.2, R_CL1.2, R_RESET.2, TP16.TP, U1.3 (!WP!(IO2)), U1.7 (!HOLD!/!RESET!(IO3)), U1.8 (VCC), U2.2 (3V3), U3.2 (VCC)
32KHZ: R2-PINH1.1, U2.9 (IO1), U3.1 (32KHZ)
DN: D1.4 (I/O2_2), J2.A7, J2.B7
DP: D1.6 (I/O1_2), J2.A6, J2.B6
EPD_3V3: C7.1, EPD_C5.2, J1.15, J1.16, L1.2, Q2.2 (S), TP17.TP
EPD_3V3_C: Q2.1 (G), R_CL1.1, TP13.TP, U2.18 (IO20)
EPD_BUSY: J1.9, TP9.TP, U2.26 (IO3)
EPD_CS: D6.2, J1.12, R9.1, TP10.TP, U2.11 (IO10)
EPD_DC: J1.11, TP11.TP, U2.5 (IO5)
EPD_RST: J1.10, TP12.TP, U2.21 (IO23)
FLASH_CS: D9.2, R5.1, U1.1 (!CS), U2.12 (IO11)
GDR: J1.2, Q1.1 (G), R4.2
GND: BOOT_BUTTON.1, BOOT_BUTTON.2, C1.2, C1_BAT.2, C1_BAT1.2, C1_BAT2.2, C2.2, C2_BAT.2, C3.-, C4_USB.2, C5.2, C5_USB.2, C6.2, C7.2, C8.2, C9.2, C10.2, C10_SUPERCAP.1, CHANGE_BUTTON.1, CHANGE_BUTTON.2, C_DELAY.2, D1.2 (GND), D3.1 (K), D6.1, D8.1, D9.1, D10.1, D11.1, D12.1, EPD_C1.1, EPD_C2.1, EPD_C5.1, EPD_C6.1, EPD_C7.1, EPD_C8.1, EPD_C9.1, EPD_C10.1, EPD_C11.1, EPD_C12.1, IC1.3 (GND), IC4.2 (VSS), J1.8, J1.17, J1.MP1, J1.MP2, J2.A1, J2.A12, J2.B1, J2.B12, J2.MP1, J2.MP2, J2.MP3, J2.MP4, J3.1, J4.G1 (GND_1), J4.G2 (GND_2), J4.G3 (GND_3), J4.G4 (GND_4), J4.P6 (VSS), R1_PWRUSB.1, R2.1, R2-USB.2, R2-USB1.1, R2_BAT.1, R4.1, RESET_BUTTON.1, RESET_BUTTON.2, SENSOR2.1 (GND), SENSOR2.5 (SDO), SENSOR2.7 (GND), SJ1.1, TP4.TP, TP5.TP, U.2 (VSS), U1.4 (GND), U1.9 (EXP), U2.1 (GND), U2.28 (GND), U2.29_1 (GND), U2.29_2 (GND), U2.29_3 (GND), U2.29_4 (GND), U2.29_5 (GND), U2.29_6 (GND), U2.29_7 (GND), U2.29_8 (GND), U2.29_9 (GND), U3.13 (GND), U4.1 (CTG), U4.4 (GND), U4.6 (QSTRT), U4.9 (EP)
GPIO8: R1.1, U2.10 (IO8)
I2C_PW: C1.1, C2.1, R1-PINH.2, R2-PINH.2, SENSOR2.2 (CSB), SENSOR2.6 (VDDIO), SENSOR2.8 (VDD), U2.17 (IO19)
INT_RTC: R1-PINH1.1, TP15.TP, U2.8 (IO0), U3.3 (SQW/!INT)
IO/BOOT: BOOT_BUTTON.3, BOOT_BUTTON.4, C6.1, R_BOOT.1, U2.15 (IO9)
IO/CHANGE: C10.1, CHANGE_BUTTON.3, CHANGE_BUTTON.4, R_CHANGE.1, U2.23 (IO15)
MISO: D12.2, J4.P7 (DAT0), R8.1, TP6.TP, U1.2 (DO(IO1)), U2.27 (IO2)
MOSI: D11.2, J1.14, J4.P3 (CMD), R7.1, TP7.TP, U1.5 (DI(IO0)), U2.7 (IO7)
unnamed: J2.A5, R2-USB1.2
unnamed: J2.B5, R2-USB.1
unnamed: C4.1, D3.2 (A), D4.1 (K)
unnamed: EPD_C2.2, J1.5
unnamed: EPD_C1.2, J1.4
unnamed: EPD_C6.2, J1.18
unnamed: EPD_C8.2, J1.20
unnamed: EPD_C7.2, J1.19
unnamed: EPD_C12.2, J1.24
unnamed: EPD_C10.2, J1.22
unnamed: D7.1 (CATHODE), R_CAPACITOR.1
unnamed: C1_BAT1.1, D2.1 (CATHODE), IC4.1 (VIN), IC4.3 (CE), Q3.2 (S)
unnamed: R1_BAT.2, U.1 (STAT)
unnamed: GHC_LED.C, R1_BAT.1
unnamed: C_DELAY.1, IC1.5 (CT)
unnamed: R2_BAT.2, U.5 (PROG)
PREVGH: D5.1 (K), EPD_C9.2, J1.21
PREVGL: D4.2 (A), EPD_C11.2, J1.23
RESE: J1.3, Q1.2 (S), R3.2, SJ1.2
RESE': R2.2, R3.1
RESET: C5.1, IC1.1 (VOUT), RESET_BUTTON.3, RESET_BUTTON.4, R_RESET.1, U2.3 (EN)
RTC_RST: U2.16 (IO18), U3.4 (!RST)
RX: TP2.TP, U2.24 (RXD0/GPIO17)
SCK: D10.2, J1.13, J4.P5 (CLK), R6.1, TP8.TP, U1.6 (CLK), U2.6 (IO6)
SCL: J3.4, R2-PINH.1, SENSOR2.4 (SCK), U2.20 (IO22), U3.16 (SCL), U4.7 (SCL)
SDA: J3.3, R1-PINH.1, SENSOR2.3 (SDI), U2.19 (IO21), U3.15 (SDA), U4.8 (SDA)
SRC: C4.2, D5.2 (A), L1.1, Q1.3 (D)
SS_SD: D8.2, J4.P2 (CD/DAT3), R10.1, U2.4 (IO4)
TX: TP1.TP, U2.25 (TXD0/GPIO16)
USB_D+: D1.1 (I/O1_1), U2.14 (IO13)
USB_D-: D1.3 (I/O2_1), U2.13 (IO12)
VBAT: C2_BAT.1, Q3.3 (D), TP3.TP, U.3 (VBAT), U4.2 (CELL), U4.3 (VDD)
VBUS: C1_BAT.1, C4_USB.1, C5_USB.1, D1.5 (VBUS), D2.2 (ANODE), GHC_LED.A, PFMF.050.1.2, Q3.1 (G), R1_PWRUSB.2, TP14.TP, U.4 (VIN)
VRTC: C8.1, C10_SUPERCAP.2, R_CAPACITOR.2, U3.14 (VBAT)
VUSB: J2.A4, J2.A9, J2.B4, J2.B9, PFMF.050.1.1

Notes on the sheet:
USB C connector & ESD protection
LDO Voltage Regulator
SD Card
ESP32 C6
Display Type Selector
E-Paper Drive Circuit
Li-Po Battery Charging Controller
Battery ChargeLevel
Voltage Supervisor + Reset & Boot / IO Button
Environmental Sensor BME688
EPD Power
E-Paper Display Header
RTC Module DS3231SN
Test Pads
Qwiic / Stemma QT
SPI ESD Protection Lines
External NOR Flash64MB

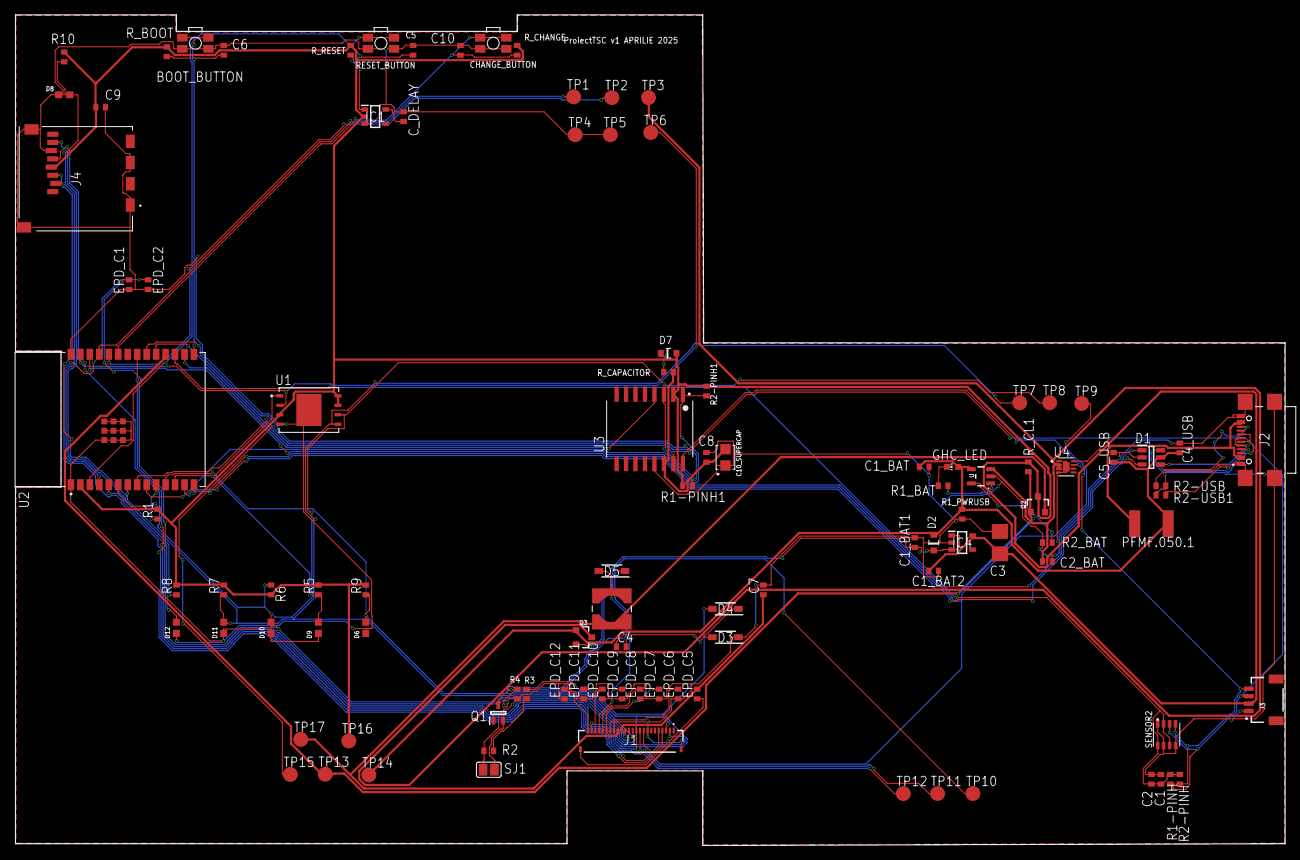
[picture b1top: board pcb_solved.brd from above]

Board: 2 copper layers, 170.3 x 111.4 mm, 103 parts (0 on the bottom side), 55 nets.

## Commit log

2025-04-06 Create as
2025-04-06 Create LICENSE
2025-04-06 Create a
2025-04-06 Rename README to README.md

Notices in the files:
parts and their libraries:
COPYRIGHT: Copyright (C) 2024 Ultra Librarian. All rights reserved.
